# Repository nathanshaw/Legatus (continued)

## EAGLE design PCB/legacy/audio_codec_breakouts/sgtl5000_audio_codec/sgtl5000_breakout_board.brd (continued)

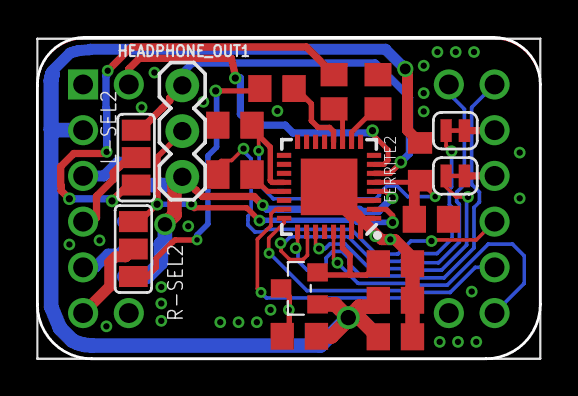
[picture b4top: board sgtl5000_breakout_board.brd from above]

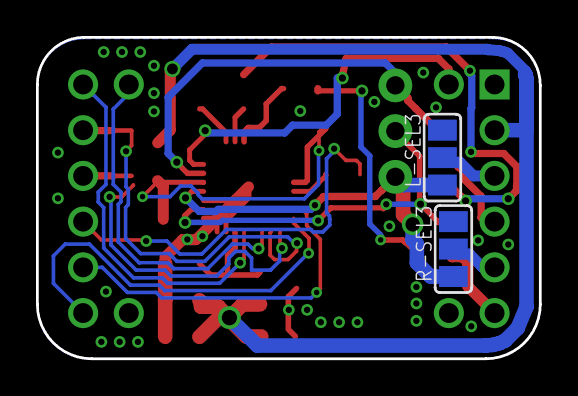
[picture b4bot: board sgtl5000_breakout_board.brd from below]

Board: 2 copper layers, 27.9 x 17.9 mm, 21 parts (2 on the bottom side), 27 nets.

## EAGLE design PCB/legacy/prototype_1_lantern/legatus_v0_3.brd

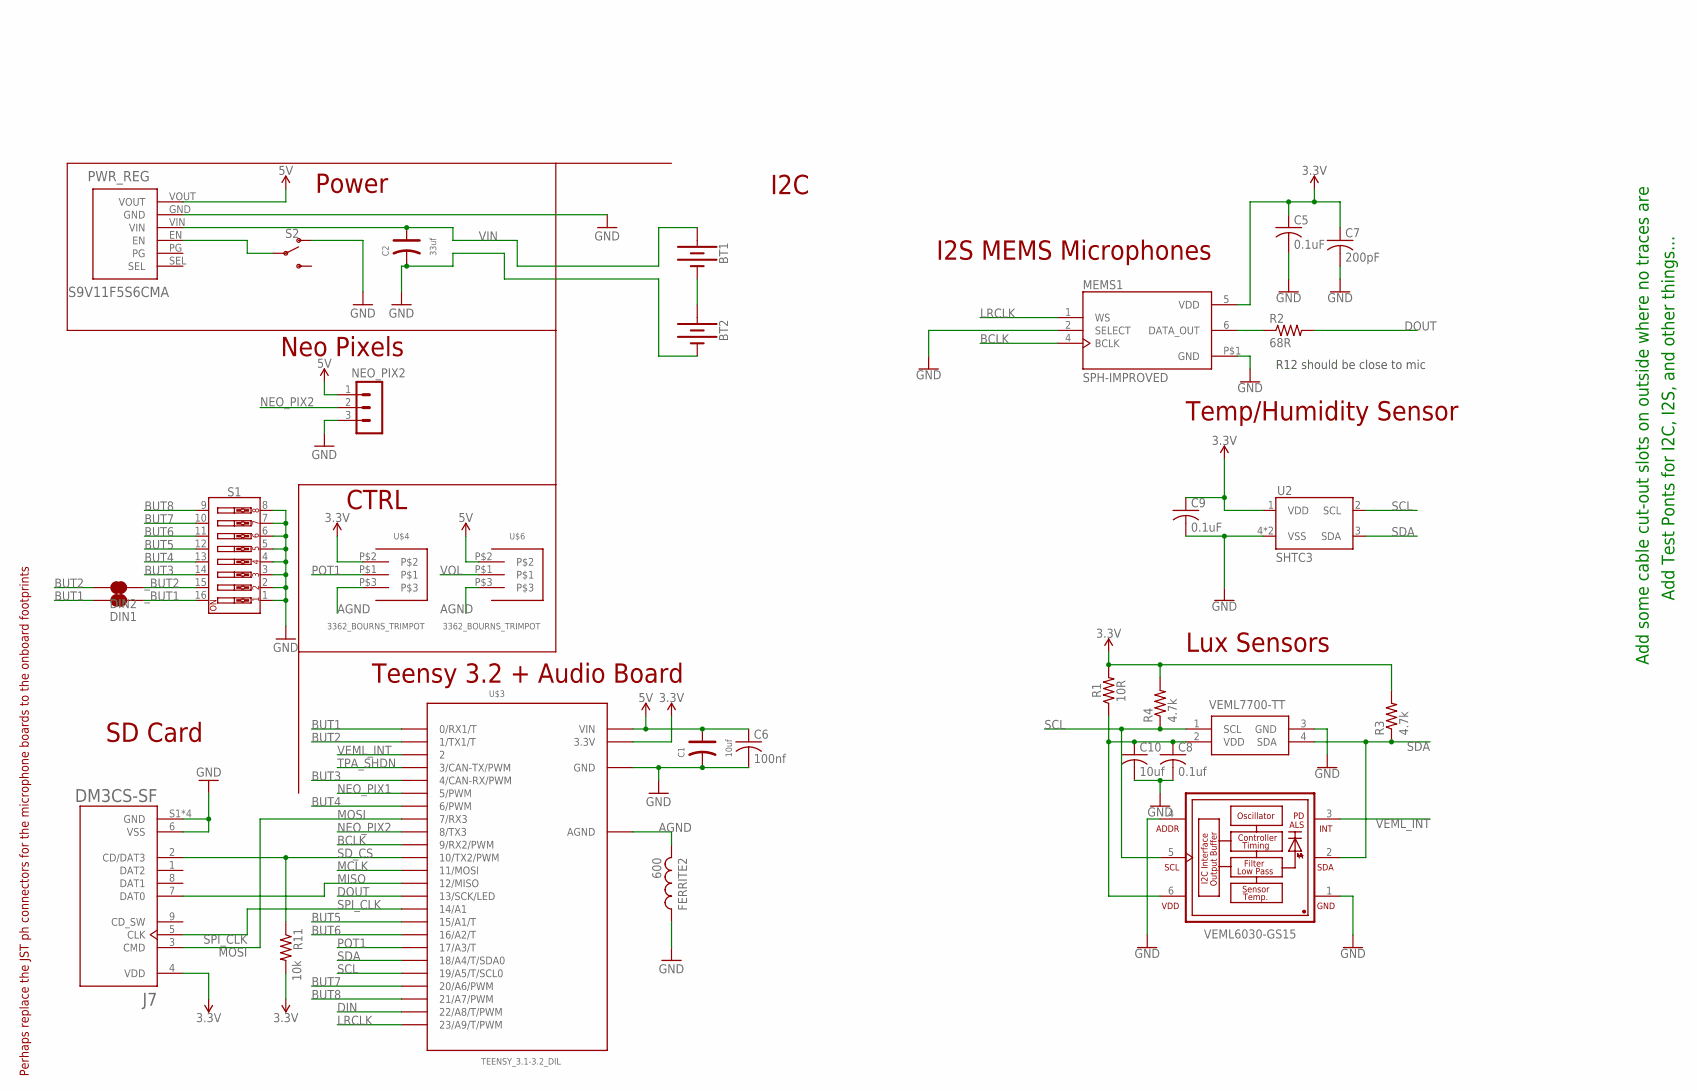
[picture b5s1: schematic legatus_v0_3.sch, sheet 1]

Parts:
BT1, BT2: BATTERY-18650; BATTERY_18650-HOLDER
C1: 10uf; PC-D5.3MM
C2: 33uf; PC-D5.3MM
C5, C9: 0.1uF; C0805
C6: 100nf; C2012
C7: 200pF; C0805
C8: 0.1uf; C0805
C10: 10uf; C0805
DIN1, DIN2: JUMPER-SMT_2_NC_TRACE_SILK; SMT-JUMPER_2_NC_TRACE_SILK
FERRITE2: 600; RESC0805_N
J7: DM3CS-SF; HRS_DM3CS-SF
MEMS1: SPH-IMPROVED; MIC_SPH0645LM4H-B_LARGER_RING
NEO_PIX2: B3B-PH-K
PWR_REG: S9V11F5S6CMA; S9V11F3S5CMA
R1: 10R; R0805
R2: 68R; M0805
R3, R4: 4.7k; M0805
R11: 10k; M0805
S1: DIP-08-PTH; DIPSWITCH-08
S2: SWITCH-SPDT-PTH-11.6X4.0MM-LOCK; SWITCH_SPDT_PTH_11.6X4.0MM_LOCK
U2: SHTC3
U$3: TEENSY_3.1-3.2_DIL; TEENSY_3.0-3.2&LC_DIL
U$4, U$6: 3362_BOURNS_TRIMPOT
VEML1: VEML7700-TT; VEML7700
VMEL1: VEML6030-GS15; VISHAY_VEML6030_2X2X0.87

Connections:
3.3V: C5.1, C7.1, C9.1, J7.4 (VDD), MEMS1.5 (VDD), R1.2, R3.2, R4.2, R11.2, U2.1 (VDD), U$3.3.3V, U$4.P$2; also elsewhere on the board
5V: C1.+, C6.1, NEO_PIX2.1, PWR_REG.VOUT, U$3.VIN, U$6.P$2; also elsewhere on the board
AGND: FERRITE2.2, U$3.AGND, U$4.P$3, U$6.P$3; also elsewhere on the board
BCLK: MEMS1.4 (BCLK), U$3.9 (9/RX2/PWM); also elsewhere on the board
BUT1: DIN1.1, U$3.0 (0/RX1/T)
BUT2: DIN2.1, U$3.1 (1/TX1/T)
BUT3: S1.14, U$3.4 (4/CAN-RX/PWM)
BUT4: S1.13, U$3.6 (6/PWM)
BUT5: S1.12, U$3.15/A1 (15/A1/T)
BUT6: S1.11, U$3.16/A2 (16/A2/T)
BUT7: S1.10, U$3.20/A6 (20/A6/PWM)
BUT8: S1.9, U$3.21/A7 (21/A7/PWM)
DIN: U$3.22/A8 (22/A8/T/PWM); also elsewhere on the board
DOUT: R2.2, U$3.13 (13/SCK/LED); also elsewhere on the board
GND: BT2.GND@1 (-), C1.-, C2.-, C5.2, C6.2, C7.2, C8.2, C9.2, C10.2, FERRITE2.1, J7.6 (VSS), J7.S1 (GND), J7.S2 (GND), J7.S3 (GND), J7.S5 (GND), MEMS1.2 (SELECT), MEMS1.P$1 (GND), NEO_PIX2.3, PWR_REG.GND, S1.1, S1.2, S1.3, S1.4, S1.5, S1.6, S1.7, S1.8, S2.1 (O), U2.4 (VSS), U2.5 (VSS), U$3.GND, VEML1.3 (GND), VMEL1.1 (GND), VMEL1.4 (ADDR); also elsewhere on the board
LRCLK: MEMS1.1 (WS), U$3.23/A9 (23/A9/T/PWM); also elsewhere on the board
MCLK: U$3.11 (11/MOSI); also elsewhere on the board
MISO: J7.7 (DAT0), U$3.12 (12/MISO)
MOSI: J7.3 (CMD), U$3.7 (7/RX3)
unnamed: MEMS1.6 (DATA_OUT), R2.1
unnamed: C8.1, C10.1, R1.1, VEML1.2 (VDD), VMEL1.6 (VDD)
unnamed: PWR_REG.EN, S2.2
unnamed: BT1.GND@1 (-), BT2.PWR@1 (+)
NEO_PIX1: U$3.5 (5/PWM); also elsewhere on the board
NEO_PIX2: NEO_PIX2.2, U$3.8 (8/TX3)
POT1: U$3.17/A3 (17/A3/T), U$4.P$1
SCL: R4.1, U2.2 (SCL), U$3.19/A5 (19/A5/T/SCL0), VEML1.1 (SCL), VMEL1.5 (SCL); also elsewhere on the board
SDA: R3.1, U2.3 (SDA), U$3.18/A4 (18/A4/T/SDA0), VEML1.4 (SDA), VMEL1.2 (SDA); also elsewhere on the board
SD_CS: J7.2 (CD/DAT3), R11.1, U$3.10 (10/TX2/PWM)
SPI_CLK: J7.5 (CLK), U$3.14/A0 (14/A1)
TPA_SHDN: U$3.3 (3/CAN-TX/PWM); also elsewhere on the board
VEML_INT: U$3.2, VMEL1.3 (INT)
VIN: BT1.PWR@1 (+), C2.+, PWR_REG.VIN
VOL: U$6.P$1; also elsewhere on the board
_BUT1: DIN1.2, S1.16
_BUT2: DIN2.2, S1.15

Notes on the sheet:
Neo Pixels
I2C
Teensy 3.2 + Audio Board
Power
CTRL
Add Test Ponts for I2C, I2S, and other things...
Add some cable cut-out slots on outside where no traces are
Perhaps replace the JST ph connectors for the microphone boards to the onboard footprints
I2S MEMS Microphones
R12 should be close to mic
Temp/Humidity Sensor
10R
Lux Sensors
SD Card

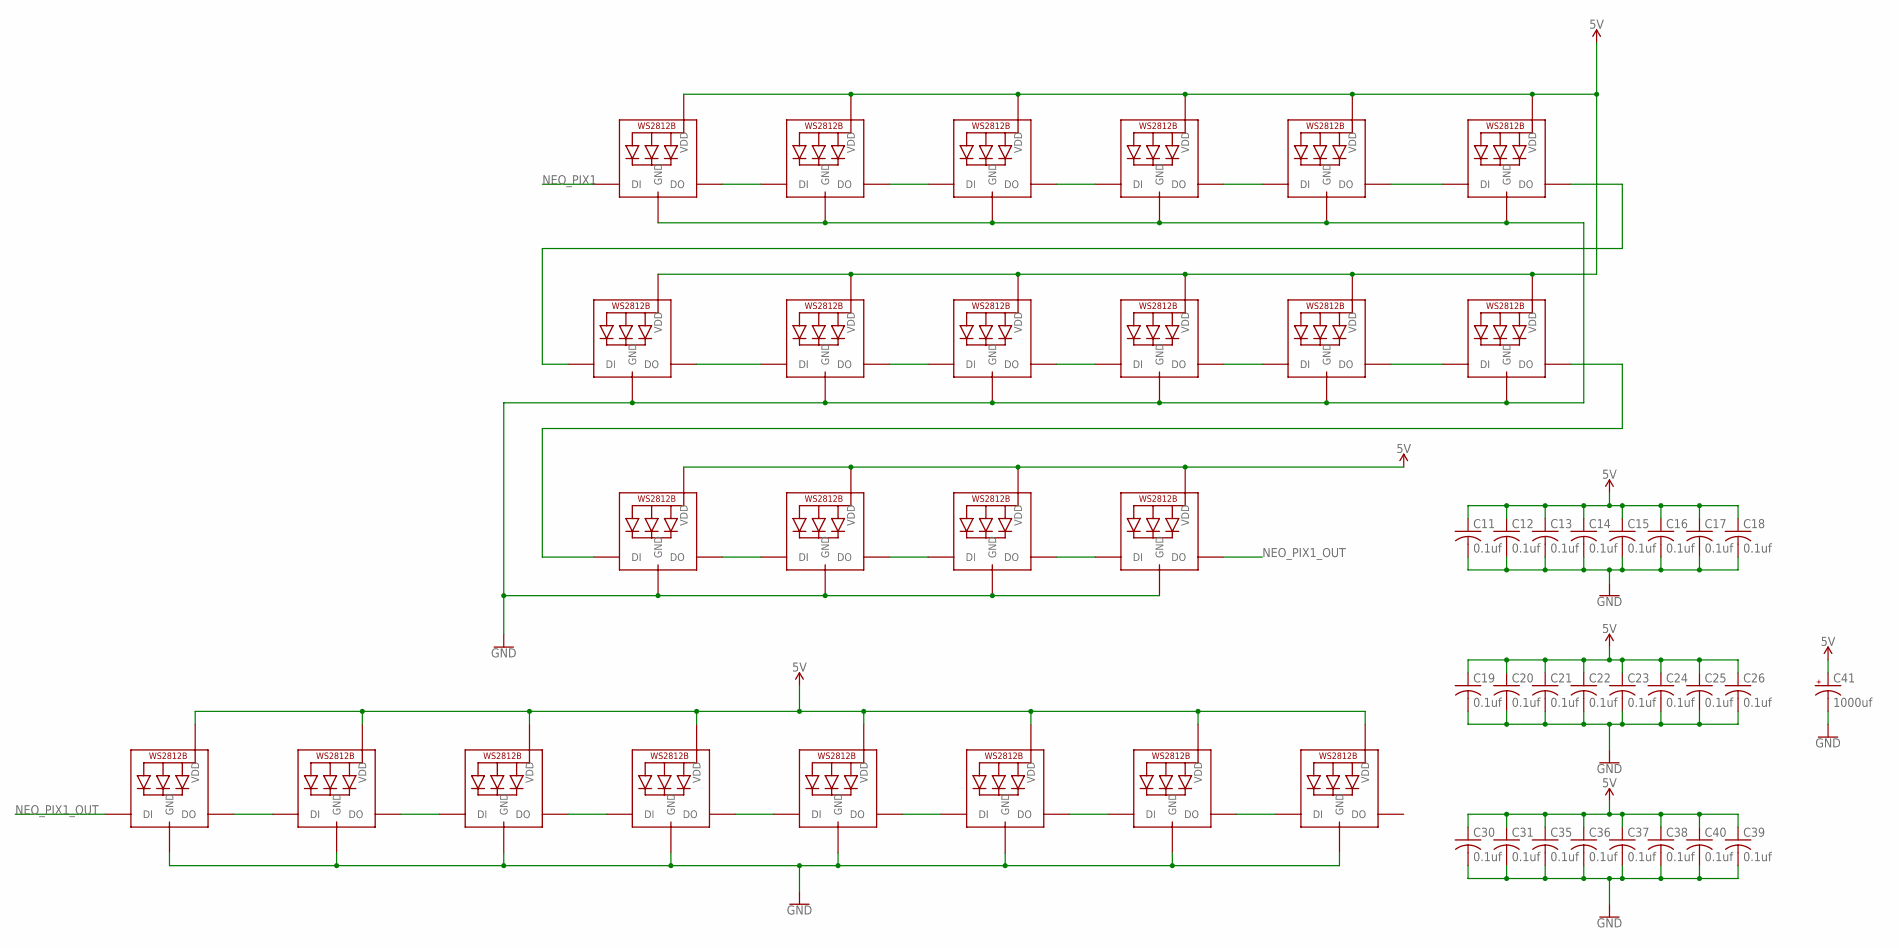
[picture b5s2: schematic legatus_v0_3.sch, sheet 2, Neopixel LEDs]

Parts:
C11, C12, C13, C14, C15, C16, C17, C18, C19, C20, C21, C22, C23, C24, C25, C26, C30, C31, C35, C36, C37, C38, C39, C40: 0.1uf; C0805
C41: 1000uf; 153CLV-1010
LED1, LED2, LED3, LED4, LED5, LED6, LED7, LED8, LED9, LED10, LED11, LED12, LED13, LED14, LED15, LED16, LED17, LED18, LED19, LED20, LED21, LED22, LED23, LED24: WS2812B_5050N; WS2812B-NARROW

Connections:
5V: C11.1, C12.1, C13.1, C14.1, C15.1, C16.1, C17.1, C18.1, C19.1, C20.1, C21.1, C22.1, C23.1, C24.1, C25.1, C26.1, C30.1, C31.1, C35.1, C36.1, C37.1, C38.1, C39.1, C40.1, C41.+, LED1.1-VDD (VDD), LED2.1-VDD (VDD), LED3.1-VDD (VDD), LED4.1-VDD (VDD), LED5.1-VDD (VDD), LED6.1-VDD (VDD), LED7.1-VDD (VDD), LED8.1-VDD (VDD), LED9.1-VDD (VDD), LED10.1-VDD (VDD), LED11.1-VDD (VDD), LED12.1-VDD (VDD), LED13.1-VDD (VDD), LED14.1-VDD (VDD), LED15.1-VDD (VDD), LED16.1-VDD (VDD), LED17.1-VDD (VDD), LED18.1-VDD (VDD), LED19.1-VDD (VDD), LED20.1-VDD (VDD), LED21.1-VDD (VDD), LED22.1-VDD (VDD), LED23.1-VDD (VDD), LED24.1-VDD (VDD); also elsewhere on the board
GND: C11.2, C12.2, C13.2, C14.2, C15.2, C16.2, C17.2, C18.2, C19.2, C20.2, C21.2, C22.2, C23.2, C24.2, C25.2, C26.2, C30.2, C31.2, C35.2, C36.2, C37.2, C38.2, C39.2, C40.2, C41.-, LED1.3-GND (GND), LED2.3-GND (GND), LED3.3-GND (GND), LED4.3-GND (GND), LED5.3-GND (GND), LED6.3-GND (GND), LED7.3-GND (GND), LED8.3-GND (GND), LED9.3-GND (GND), LED10.3-GND (GND), LED11.3-GND (GND), LED12.3-GND (GND), LED13.3-GND (GND), LED14.3-GND (GND), LED15.3-GND (GND), LED16.3-GND (GND), LED17.3-GND (GND), LED18.3-GND (GND), LED19.3-GND (GND), LED20.3-GND (GND), LED21.3-GND (GND), LED22.3-GND (GND), LED23.3-GND (GND), LED24.3-GND (GND); also elsewhere on the board
unnamed: LED1.2-DOUT (DO), LED2.4-DIN (DI)
unnamed: LED2.2-DOUT (DO), LED3.4-DIN (DI)
unnamed: LED3.2-DOUT (DO), LED4.4-DIN (DI)
unnamed: LED4.2-DOUT (DO), LED5.4-DIN (DI)
unnamed: LED5.2-DOUT (DO), LED6.4-DIN (DI)
unnamed: LED7.2-DOUT (DO), LED8.4-DIN (DI)
unnamed: LED8.2-DOUT (DO), LED9.4-DIN (DI)
unnamed: LED9.2-DOUT (DO), LED10.4-DIN (DI)
unnamed: LED10.2-DOUT (DO), LED11.4-DIN (DI)
unnamed: LED11.2-DOUT (DO), LED12.4-DIN (DI)
unnamed: LED13.2-DOUT (DO), LED14.4-DIN (DI)
unnamed: LED14.2-DOUT (DO), LED15.4-DIN (DI)
unnamed: LED15.2-DOUT (DO), LED16.4-DIN (DI)
unnamed: LED12.2-DOUT (DO), LED13.4-DIN (DI)
unnamed: LED6.2-DOUT (DO), LED7.4-DIN (DI)
unnamed: LED18.2-DOUT (DO), LED19.4-DIN (DI)
unnamed: LED19.2-DOUT (DO), LED20.4-DIN (DI)
unnamed: LED20.2-DOUT (DO), LED21.4-DIN (DI)
unnamed: LED21.2-DOUT (DO), LED22.4-DIN (DI)
unnamed: LED22.2-DOUT (DO), LED23.4-DIN (DI)
unnamed: LED23.2-DOUT (DO), LED24.4-DIN (DI)
unnamed: LED17.2-DOUT (DO), LED18.4-DIN (DI)
NEO_PIX1: LED1.4-DIN (DI); also elsewhere on the board
NEO_PIX1_OUT: LED16.2-DOUT (DO), LED17.4-DIN (DI)

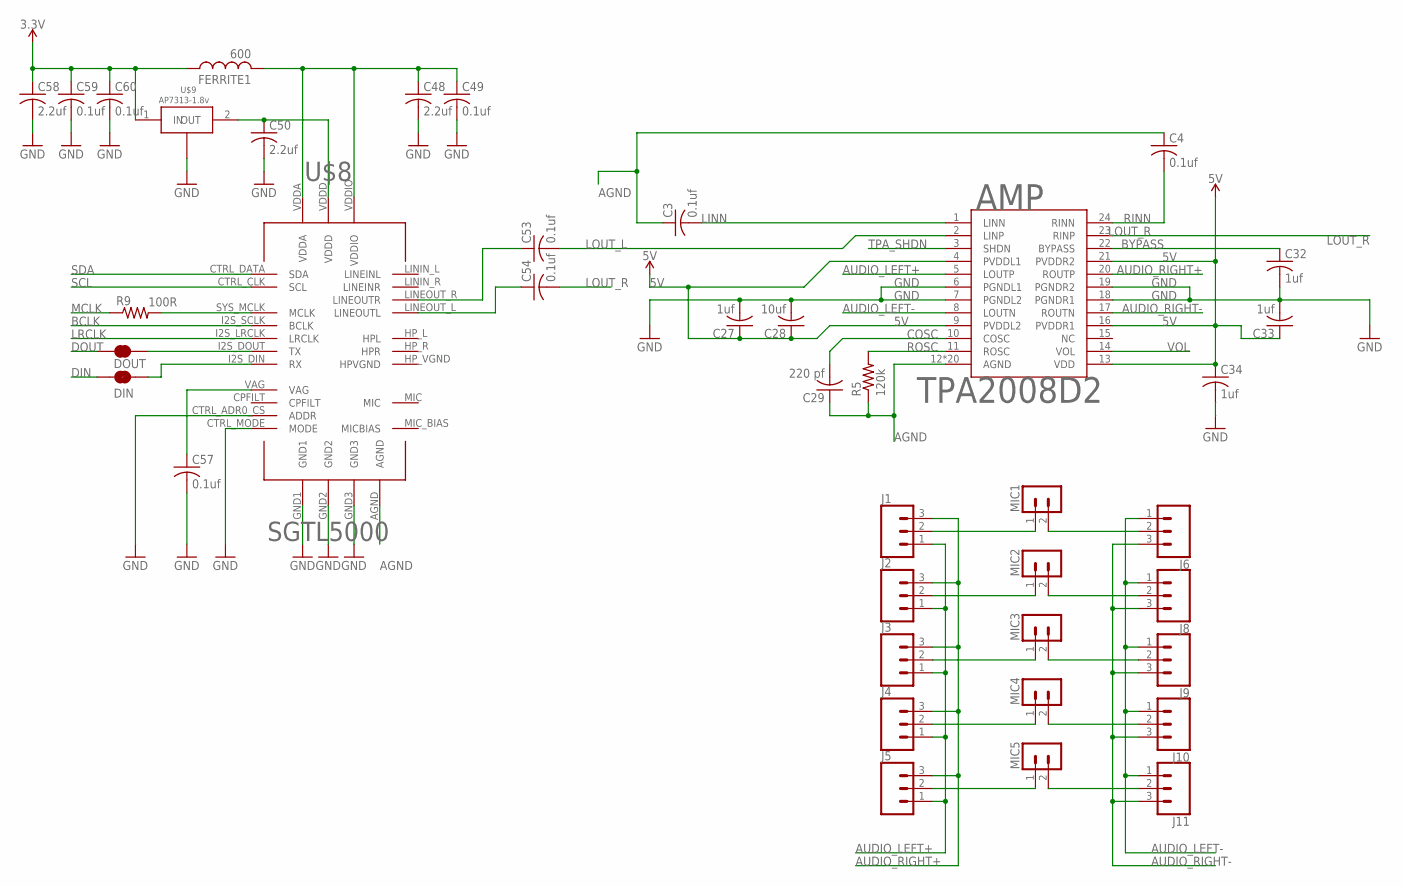
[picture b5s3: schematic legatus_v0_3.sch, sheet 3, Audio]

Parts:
AMP: TPA2008D2; PWP-TSSOP24
C3, C4, C49, C53, C54, C57, C59, C60: 0.1uf; C0805
C27, C32, C33, C34: 1uf; C0805
C28: 10uf; C0805
C29: 220 pf; C0805
C48, C50, C58: 2.2uf; C0805
DIN: JUMPER-SMT_2_NC_TRACE_SILK; SMT-JUMPER_2_NC_TRACE_SILK
DOUT: JUMPER-SMT_2_NC_TRACE_SILK; SMT-JUMPER_2_NC_TRACE_SILK
FERRITE1: 600; RESC0805_N
J1, J2, J3, J4, J5, J6, J8, J9, J10, J11: CONN_03; 1X03
MIC1, MIC2, MIC3, MIC4, MIC5: B2B-PH-K
R5: 120k; M0805
R9: 100R; M0805
U$8: SGTL5000; QFN-32-5X5MM
U$9: AP7313-1.8v; SOT-23

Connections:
3.3V: C58.1, C59.1, C60.1, FERRITE1.1, U$9.1 (IN); also elsewhere on the board
5V: AMP.4 (PVDDL1), AMP.9 (PVDDL2), AMP.13 (VDD), AMP.16 (PVDDR1), AMP.21 (PVDDR2), C27.1, C28.1, C33.1, C34.1; also elsewhere on the board
AGND: AMP.12 (AGND), AMP.EXP (AGND), AMP.EXP@1 (AGND), AMP.EXP@2 (AGND), AMP.EXP@3 (AGND), AMP.EXP@4 (AGND), AMP.EXP@5 (AGND), AMP.EXP@6 (AGND), AMP.EXP@7 (AGND), AMP.EXP@8 (AGND), AMP.EXP@9 (AGND), AMP.EXP@10 (AGND), AMP.EXP@11 (AGND), AMP.EXP@12 (AGND), AMP.EXP@13 (AGND), AMP.EXP@14 (AGND), AMP.EXP@15 (AGND), AMP.EXP@16 (AGND), AMP.EXP@17 (AGND), AMP.EXP@18 (AGND), C3.1, C4.1, C29.1, R5.1, U$8.AGND; also elsewhere on the board
AUDIO_LEFT+: AMP.5 (LOUTP), J1.1, J2.1, J3.1, J4.1, J5.1
AUDIO_LEFT-: AMP.8 (LOUTN), J6.1, J8.1, J9.1, J10.1, J11.1
AUDIO_RIGHT+: AMP.20 (ROUTP), J1.3, J2.3, J3.3, J4.3, J5.3
AUDIO_RIGHT-: AMP.17 (ROUTN), J6.3, J8.3, J9.3, J10.3, J11.3
BCLK: U$8.I2S_SCLK (BCLK); also elsewhere on the board
BYPASS: AMP.22 (BYPASS), C32.1
COSC: AMP.10 (COSC), C29.2
DIN: DIN.1; also elsewhere on the board
DOUT: DOUT.1; also elsewhere on the board
EDITROUTE: C48.1, C49.1, FERRITE1.2, U$8.VDDA, U$8.VDDIO
GND: AMP.6 (PGNDL1), AMP.7 (PGNDL2), AMP.18 (PGNDR1), AMP.19 (PGNDR2), C27.2, C28.2, C32.2, C33.2, C34.2, C48.2, C49.2, C50.2, C57.2, C58.2, C59.2, C60.2, U$8.CTRL_ADR0_CS (ADDR), U$8.CTRL_MODE (MODE), U$8.GND1, U$8.GND2, U$8.GND3, U$9.3 (GND); also elsewhere on the board
LINN: AMP.1 (LINN), C3.2
LOUT_L: AMP.2 (LINP), C53.2
LOUT_R: AMP.23 (RINP), C54.2
LRCLK: U$8.I2S_LRCLK (LRCLK); also elsewhere on the board
MCLK: R9.1; also elsewhere on the board
unnamed: J1.2, MIC1.1
unnamed: J2.2, MIC2.1
unnamed: J3.2, MIC3.1
unnamed: J4.2, MIC4.1
unnamed: J5.2, MIC5.1
unnamed: J6.2, MIC1.2
unnamed: C53.1, U$8.LINEOUT_R (LINEOUTR)
unnamed: C54.1, U$8.LINEOUT_L (LINEOUTL)
unnamed: J8.2, MIC2.2
unnamed: C57.1, U$8.VAG
unnamed: DIN.2, U$8.I2S_DIN (RX)
unnamed: DOUT.2, U$8.I2S_DOUT (TX)
unnamed: R9.2, U$8.SYS_MCLK (MCLK)
unnamed: C50.1, U$8.VDDD, U$9.2 (OUT)
unnamed: J9.2, MIC3.2
unnamed: J10.2, MIC4.2
unnamed: J11.2, MIC5.2
RINN: AMP.24 (RINN), C4.2
ROSC: AMP.11 (ROSC), R5.2
SCL: U$8.CTRL_CLK (SCL); also elsewhere on the board
SDA: U$8.CTRL_DATA (SDA); also elsewhere on the board
TPA_SHDN: AMP.3 (SHDN); also elsewhere on the board
VOL: AMP.14 (VOL); also elsewhere on the board

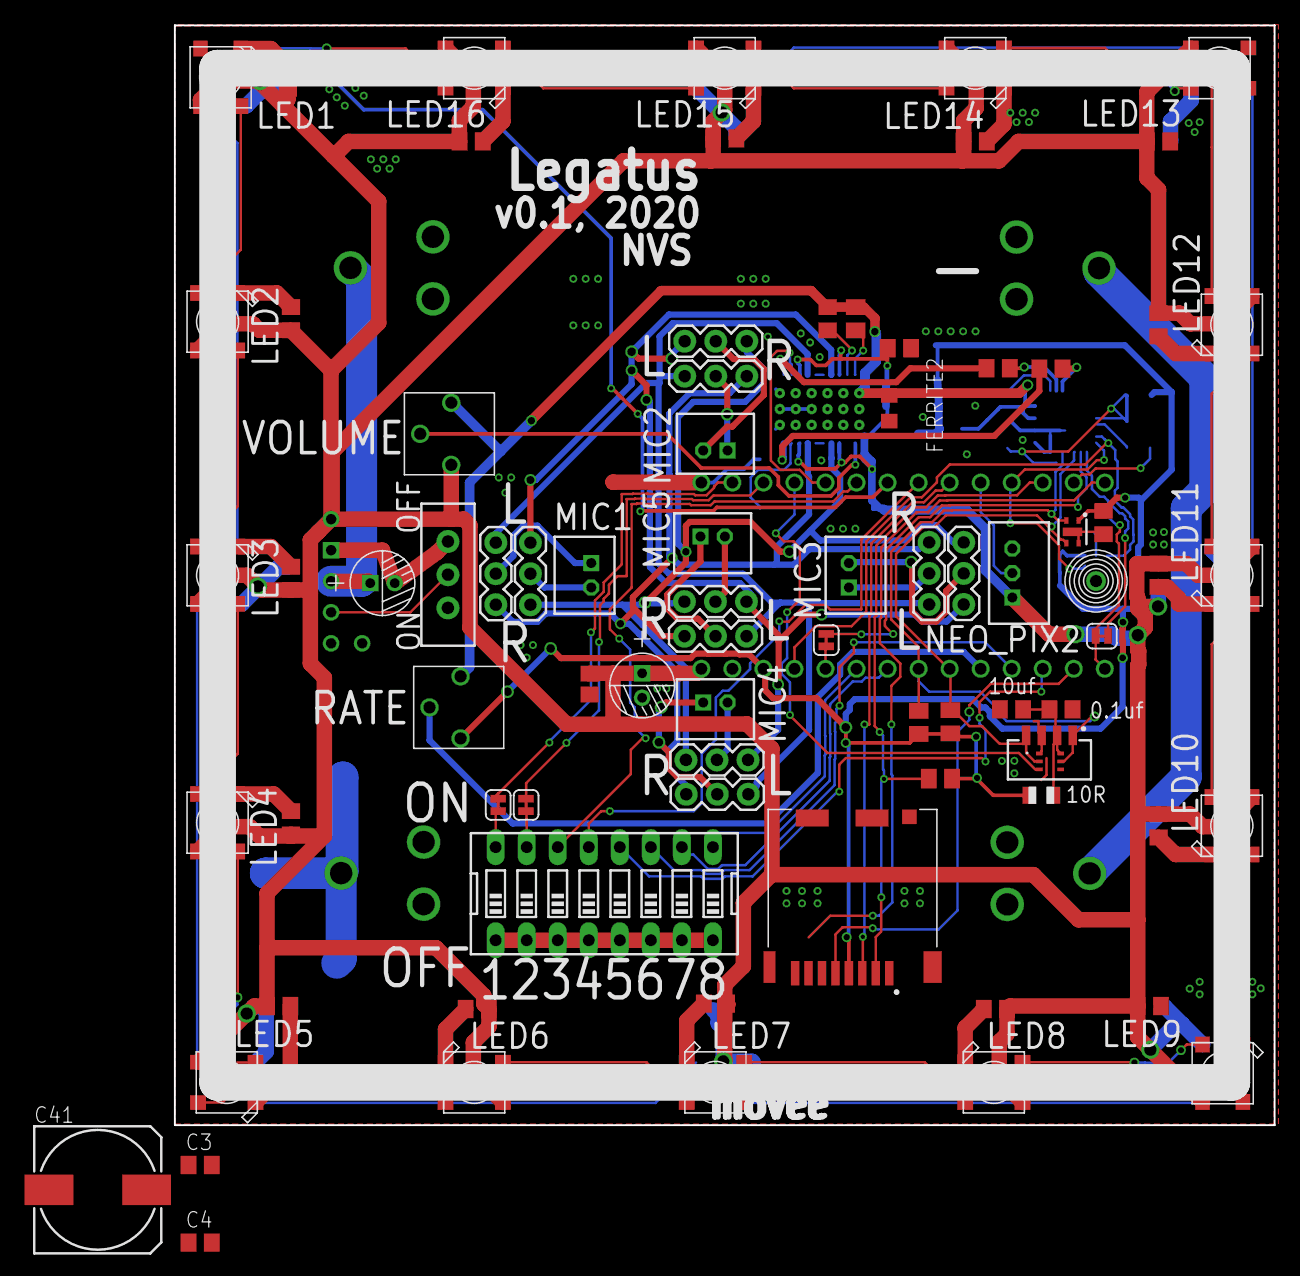
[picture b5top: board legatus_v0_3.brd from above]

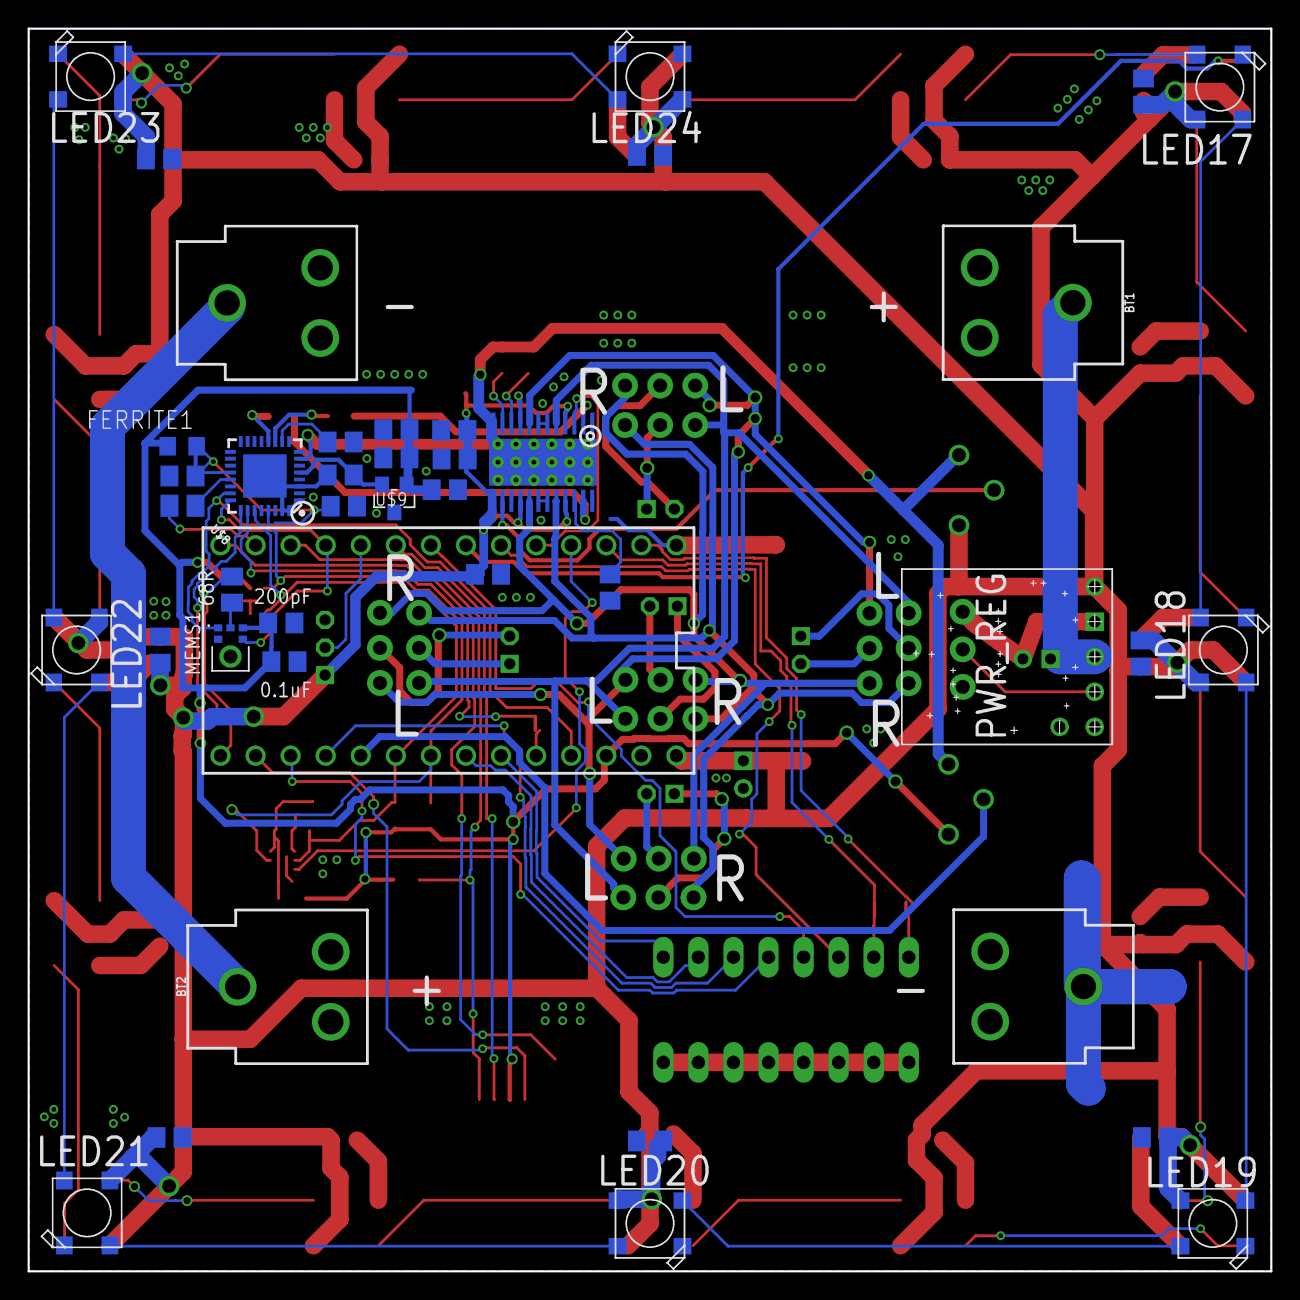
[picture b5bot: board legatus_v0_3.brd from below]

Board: 2 copper layers, 90.0 x 90.0 mm, 119 parts (40 on the bottom side), 88 nets.

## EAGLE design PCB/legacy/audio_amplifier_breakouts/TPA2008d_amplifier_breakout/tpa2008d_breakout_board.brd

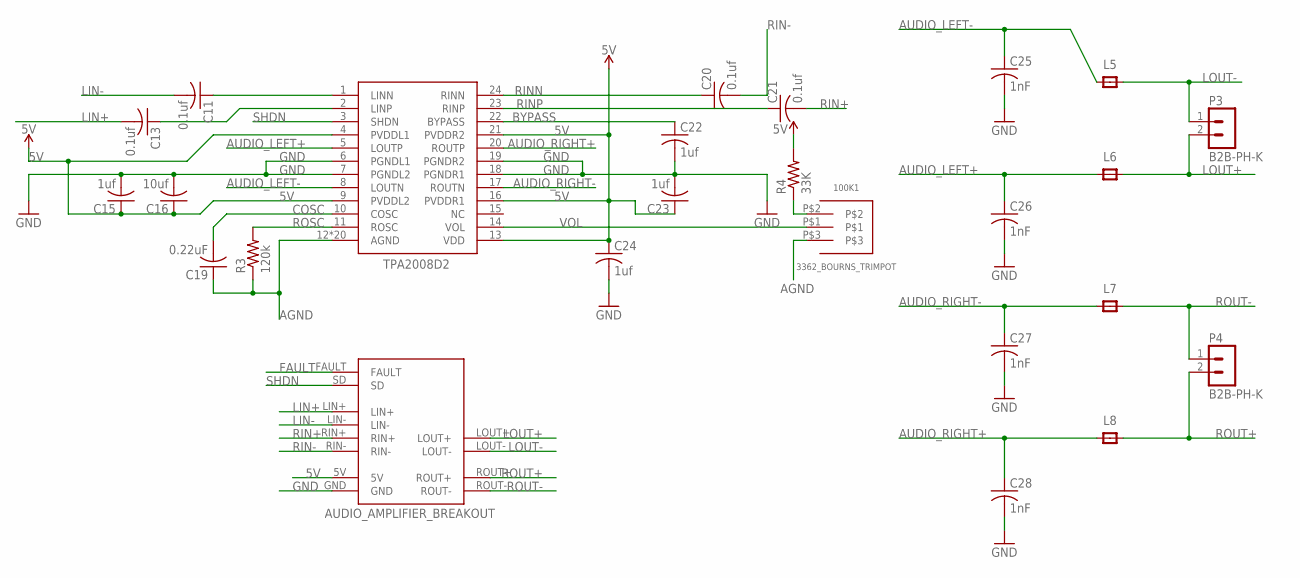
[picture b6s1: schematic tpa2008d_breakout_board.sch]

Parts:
100K1: 3362_BOURNS_TRIMPOT
C11, C13, C20, C21: 0.1uf; C0805
C15, C22, C23, C24: 1uf; C0805
C16: 10uf; C0805
C19: 0.22uF; C0805
C25, C26, C27, C28: 1nF; C0805
L5, L6, L7, L8: 600Ohm@100MHz; RC-MASTER-SMD_L1206MP
P3, P4: B2B-PH-K
R3: 120k; M0805
R4: 33K; M0805
U$2: TPA2008D2; PWP-TSSOP24
U$3: AUDIO_AMPLIFIER_BREAKOUT

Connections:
5V: C15.1, C16.1, C23.1, C24.1, R4.2, U$2.4 (PVDDL1), U$2.9 (PVDDL2), U$2.13 (VDD), U$2.16 (PVDDR1), U$2.21 (PVDDR2), U$3.5V
AGND: 100K1.P$3, C19.1, R3.1, U$2.12 (AGND), U$2.EXP (AGND), U$2.EXP@1 (AGND), U$2.EXP@2 (AGND), U$2.EXP@3 (AGND), U$2.EXP@4 (AGND), U$2.EXP@5 (AGND), U$2.EXP@6 (AGND), U$2.EXP@7 (AGND), U$2.EXP@8 (AGND), U$2.EXP@9 (AGND), U$2.EXP@10 (AGND), U$2.EXP@11 (AGND), U$2.EXP@12 (AGND), U$2.EXP@13 (AGND), U$2.EXP@14 (AGND), U$2.EXP@15 (AGND), U$2.EXP@16 (AGND), U$2.EXP@17 (AGND), U$2.EXP@18 (AGND)
AUDIO_LEFT+: C26.1, L6.1, U$2.5 (LOUTP)
AUDIO_LEFT-: C25.1, L5.1, U$2.8 (LOUTN)
AUDIO_RIGHT+: C28.1, L8.1, U$2.20 (ROUTP)
AUDIO_RIGHT-: C27.1, L7.1, U$2.17 (ROUTN)
BYPASS: C22.1, U$2.22 (BYPASS)
COSC: C19.2, U$2.10 (COSC)
FAULT: U$3.FAULT
GND: C15.2, C16.2, C22.2, C23.2, C24.2, C25.2, C26.2, C27.2, C28.2, U$2.6 (PGNDL1), U$2.7 (PGNDL2), U$2.18 (PGNDR1), U$2.19 (PGNDR2), U$3.GND
LIN+: C13.2, U$3.LIN+
LIN-: C11.2, U$3.LIN-
LINN-1: C11.1, U$2.1 (LINN)
LINP-1: C13.1, U$2.2 (LINP)
LOUT+: L6.2, P3.2, U$3.LOUT+
LOUT-: L5.2, P3.1, U$3.LOUT-
unnamed: 100K1.P$2, R4.1
RIN+: C21.2, U$3.RIN+
RIN-: C20.2, U$3.RIN-
RINN: C20.1, U$2.24 (RINN)
RINP: C21.1, U$2.23 (RINP)
ROSC: R3.2, U$2.11 (ROSC)
ROUT+: L8.2, P4.2, U$3.ROUT+
ROUT-: L7.2, P4.1, U$3.ROUT-
SHDN: U$2.3 (SHDN), U$3.SD
VOL: 100K1.P$1, U$2.14 (VOL)

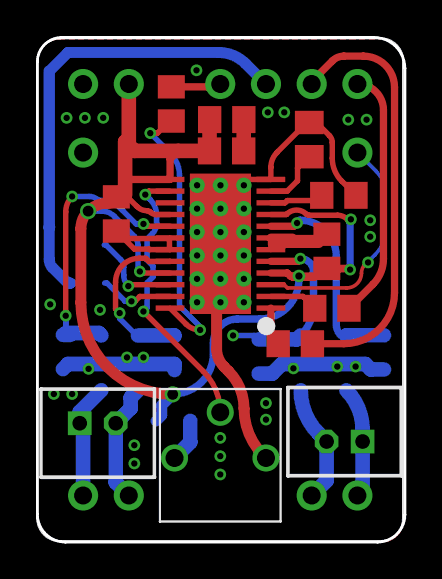
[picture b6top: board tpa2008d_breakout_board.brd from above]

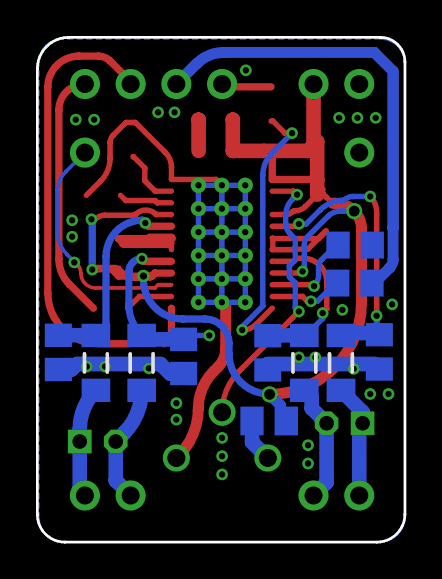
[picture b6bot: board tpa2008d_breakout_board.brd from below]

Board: 2 copper layers, 20.4 x 28.0 mm, 25 parts (11 on the bottom side), 25 nets.

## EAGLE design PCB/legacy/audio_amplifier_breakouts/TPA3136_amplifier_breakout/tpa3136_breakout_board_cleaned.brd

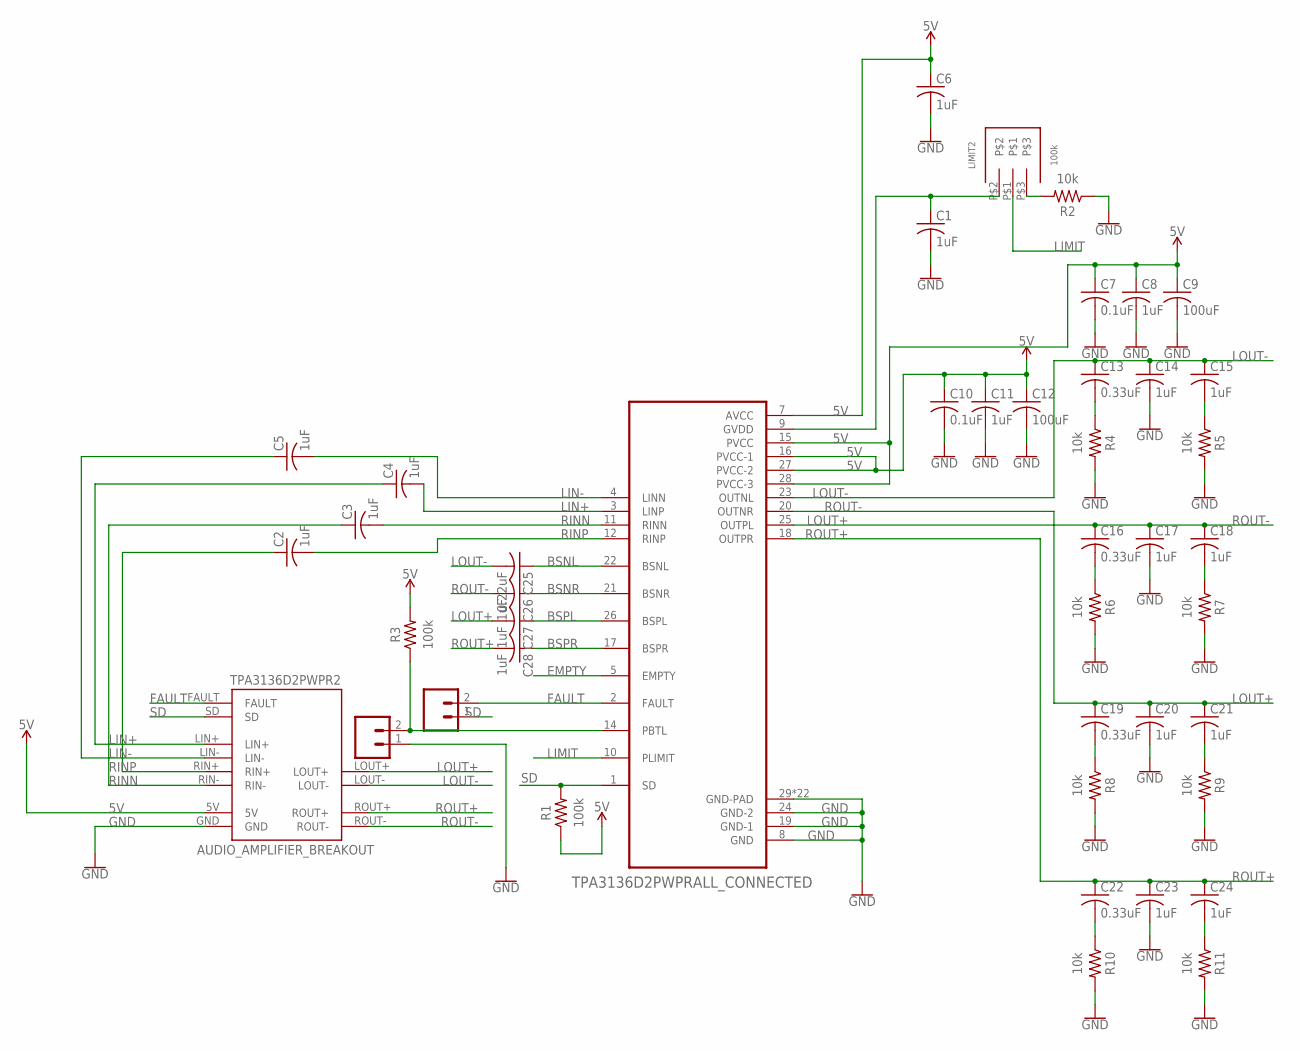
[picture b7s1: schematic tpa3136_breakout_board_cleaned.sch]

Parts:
AUTO_SHUTDOWN1, AUTO_SHUTDOWN4: CONN_02; 1X02
C1, C2, C3, C4, C5, C6, C8, C11, C14, C15, C17, C18, C20, C21, C23, C24, C26, C27, C28: 1uF; CAPC2012X110
C7, C10: 0.1uF; CAPC2012X110
C9, C12: 100uF; CAPC3216X135
C13, C16, C19, C22: 0.33uF; CAPC2012X110
C25: 0.22uF; CAPC2012X110
LIMIT2: 100k; 3362_BOURNS_TRIMPOT
R1, R3: 100k; RESC2012X65
R2, R4, R5, R6, R7, R8, R9, R10, R11: 10k; RESC2012X65
TPA3136D2PWPR2: AUDIO_AMPLIFIER_BREAKOUT
U1: TPA3136D2PWPRALL_CONNECTED; IC_TPS61196PWPRQ1

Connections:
5V: C6.1, C7.1, C8.1, C9.1, C10.1, C11.1, C12.1, R1.1, R3.2, TPA3136D2PWPR2.5V, U1.7 (AVCC), U1.15 (PVCC), U1.16 (PVCC-1), U1.27 (PVCC-2), U1.28 (PVCC-3)
ASDFSDF: AUTO_SHUTDOWN4.1
BSNL: C25.1, U1.22 (BSNL)
BSNR: C26.1, U1.21 (BSNR)
BSPL: C27.1, U1.26 (BSPL)
BSPR: C28.1, U1.17 (BSPR)
EMPTY: U1.5 (EMPTY)
FAULT: AUTO_SHUTDOWN1.2, TPA3136D2PWPR2.FAULT, U1.2 (FAULT)
GND: C1.2, C6.2, C7.2, C8.2, C9.2, C10.2, C11.2, C12.2, C14.2, C17.2, C20.2, C23.2, R2.1, R4.2, R5.2, R6.2, R7.2, R8.2, R9.2, R10.2, R11.2, TPA3136D2PWPR2.GND, U1.8 (GND), U1.19 (GND-1), U1.24 (GND-2), U1.29 (GND-PAD), U1.30 (GND-PAD), U1.31 (GND-PAD), U1.32 (GND-PAD), U1.33 (GND-PAD), U1.34 (GND-PAD), U1.35 (GND-PAD), U1.36 (GND-PAD), U1.37 (GND-PAD), U1.38 (GND-PAD), U1.39 (GND-PAD), U1.40 (GND-PAD), U1.41 (GND-PAD), U1.42 (GND-PAD), U1.43 (GND-PAD), U1.44 (GND-PAD), U1.45 (GND-PAD), U1.46 (GND-PAD), U1.47 (GND-PAD), U1.48 (GND-PAD), U1.49 (GND-PAD), U1.50 (GND-PAD)
LIMIT: LIMIT2.P$1, U1.10 (PLIMIT)
LIN+: C4.1, TPA3136D2PWPR2.LIN+
LIN-: C5.1, TPA3136D2PWPR2.LIN-
LOUT+: C19.1, C20.1, C21.1, C27.2, TPA3136D2PWPR2.LOUT+, U1.25 (OUTPL)
LOUT-: C13.1, C14.1, C15.1, C25.2, TPA3136D2PWPR2.LOUT-, U1.23 (OUTNL)
unnamed: C3.2, U1.11 (RINN)
unnamed: C2.2, U1.12 (RINP)
unnamed: C4.2, U1.3 (LINP)
unnamed: C5.2, U1.4 (LINN)
unnamed: C1.1, LIMIT2.P$2, U1.9 (GVDD)
unnamed: LIMIT2.P$3, R2.2
unnamed: C13.2, R4.1
unnamed: C15.2, R5.1
unnamed: C16.2, R6.1
unnamed: C18.2, R7.1
unnamed: C19.2, R8.1
unnamed: C21.2, R9.1
unnamed: C22.2, R10.1
unnamed: C24.2, R11.1
unnamed: AUTO_SHUTDOWN4.2, R3.1, U1.14 (PBTL)
RINN: C3.1, TPA3136D2PWPR2.RIN-
RINP: C2.1, TPA3136D2PWPR2.RIN+
ROUT+: C22.1, C23.1, C24.1, C28.2, TPA3136D2PWPR2.ROUT+, U1.18 (OUTPR)
ROUT-: C16.1, C17.1, C18.1, C26.2, TPA3136D2PWPR2.ROUT-, U1.20 (OUTNR)
SD: AUTO_SHUTDOWN1.1, R1.2, TPA3136D2PWPR2.SD, U1.1 (SD)

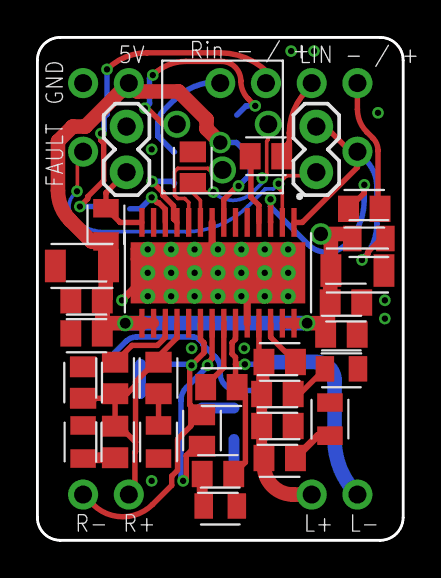
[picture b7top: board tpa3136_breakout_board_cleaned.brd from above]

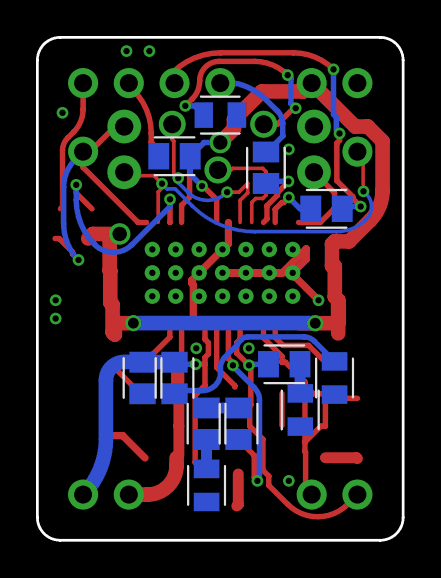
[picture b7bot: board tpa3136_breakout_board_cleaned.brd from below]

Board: 2 copper layers, 20.3 x 27.9 mm, 44 parts (12 on the bottom side), 32 nets.

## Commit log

2022-09-17 new ignore?
2022-09-17 added the schematic and layout files
2022-09-17 removed old gitignore
